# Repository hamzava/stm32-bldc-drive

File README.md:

# ⚡ Sensorless 3-Phase BLDC Motor Driver  
### Using STM32F411RE + IR2110 Gate Drivers + IRF3205

> 📌 **Recommended Reading:**  
> Please refer to `/Docs/BLDC Project Report.pdf` first for a detailed explanation of the architecture, technical challenges encountered, and lessons learned during development.  
> This repository documents a prototype exploration and does not represent a finalized, fully validated motor drive system.

◆ This project represents an exploration into low-level complementary PWM control, high-side bootstrap driving, and discrete 3-phase inverter design using STM32 advanced timers.

---

## ◆ Project Overview

🟥 This project is a  3-phase BLDC motor driver prototype built using:

 - **STM32F411RE** (Advanced Timer – Complementary PWM)
 - **IR2110 High/Low Side Gate Drivers**
 - IRF3205 N-Channel MOSFET Half-Bridges
 - Bootstrap High-Side Supply Topology

🟥 The objective was to implement manual commutation for a sensorless BLDC motor using complementary PWM outputs from the MCU’s advanced timer (TIM1), with register-level control and control the motor using it's BEMF.

This prototype focused on:

✔ BLDC Motor Control Algorithm
✔ Complementary PWM generation  
✔ Gate driver bootstrap behavior  
✔ Register-level commutation control  
✔ Hardware–firmware synchronization  

---
## ◆ Repository Structure
/Hardware
- ├── KiCad_Project
- ├── Gerbers
- ├── Schematics_PDF
- ├── PCB_Images

/Firmware

/Videos

/Docs
- ├── Datasheets
- ├── Resources_Used > ***All the files used to learn about technologies involved in this project***
- ├── BLDC Project Report.pdf

---

## ◆ Status

Prototype exploration complete.  
Further revision planned with improved instrumentation and driver selection.

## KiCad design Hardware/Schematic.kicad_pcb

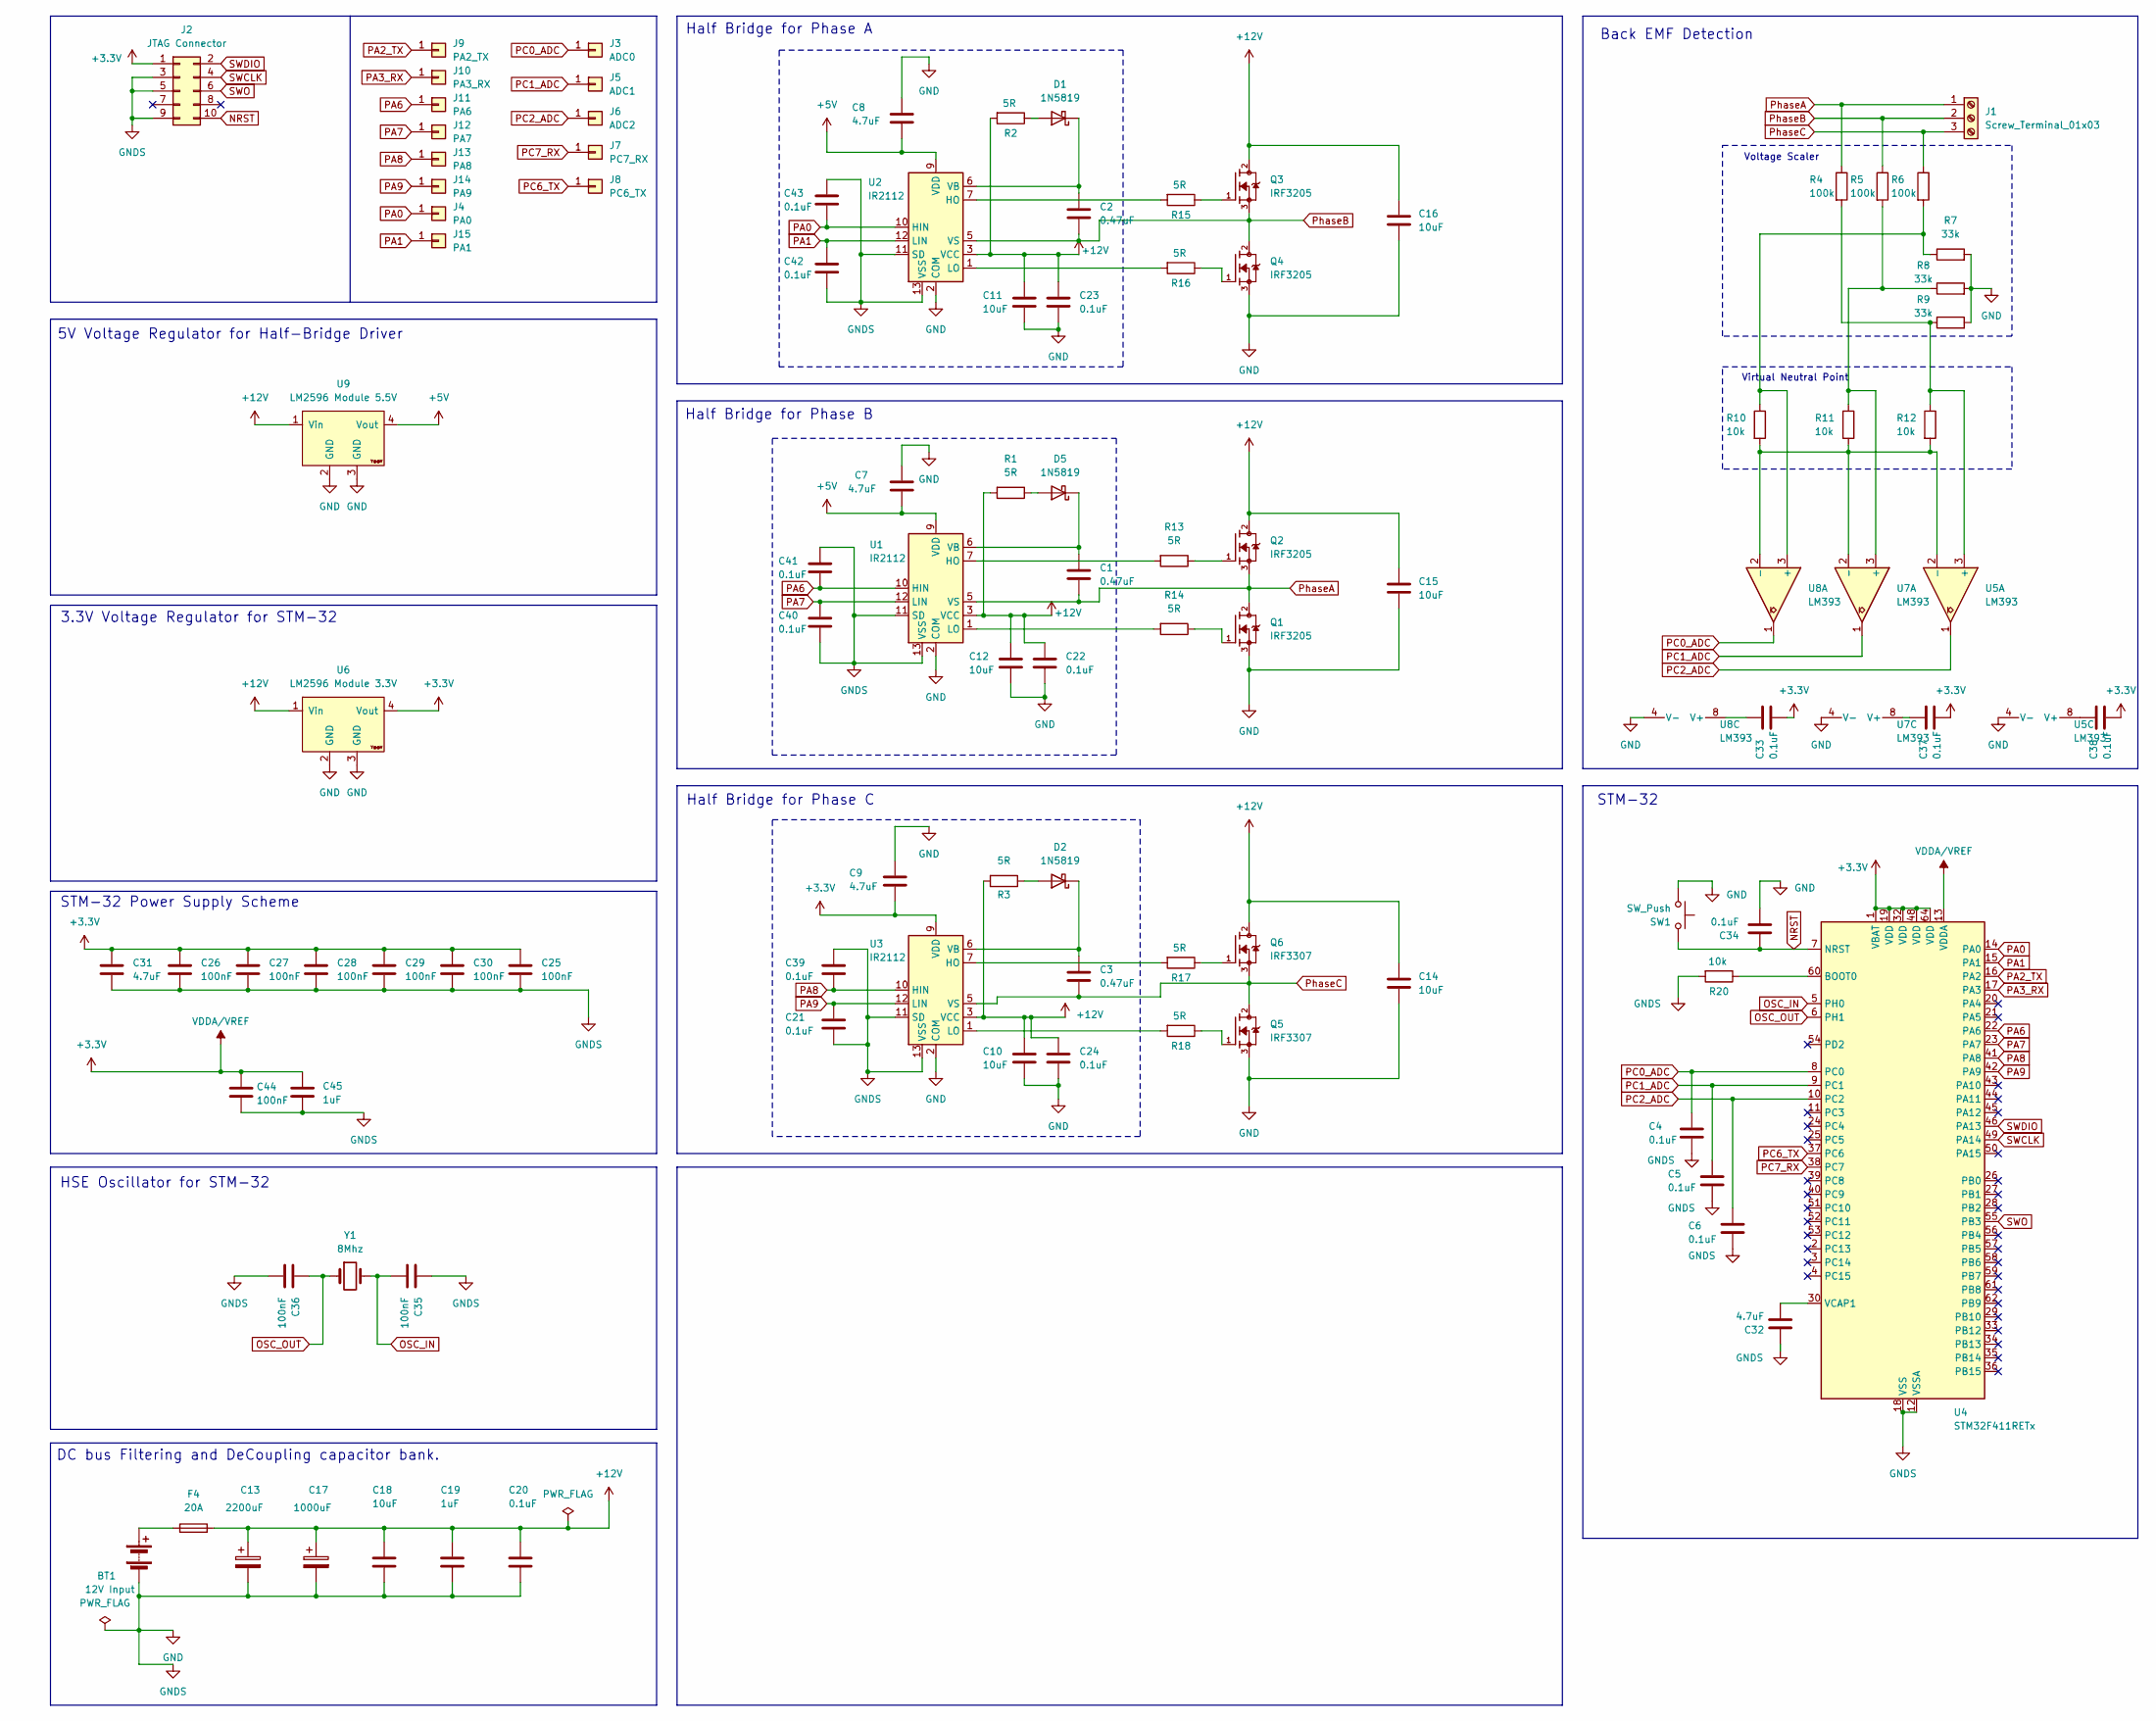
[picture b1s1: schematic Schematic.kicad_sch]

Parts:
BT1: 12V Input; AMASS_XT60-F_1x02_P7.20mm_Vertical
C1, C2, C3: 0.47uF; C_Disc_D4.3mm_W1.9mm_P5.00mm
C4, C5, C6, C20, C21, C22, C23, C24, C33, C34, C37, C38, C39, C40, C41, C42, C43: 0.1uF; C_Disc_D4.3mm_W1.9mm_P5.00mm
C7, C8, C9, C31, C32: 4.7uF; C_Disc_D4.3mm_W1.9mm_P5.00mm
C10, C11, C12, C14, C15, C16, C18: 10uF; C_Disc_D4.3mm_W1.9mm_P5.00mm
C13: 2200uF; CP_Radial_D10.0mm_P5.00mm
C17: 1000uF; CP_Radial_D8.0mm_P3.50mm
C19, C45: 1uF; C_Disc_D4.3mm_W1.9mm_P5.00mm
C25, C26, C27, C28, C29, C30, C35, C36, C44: 100nF; C_Disc_D4.3mm_W1.9mm_P5.00mm
D1, D2, D5: 1N5819; D_DO-35_SOD27_P7.62mm_Horizontal
F4: 20A; Fuseholder_Clip-5x20mm_Eaton_1A5601-01_Inline_P20.80x6.76mm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
J1: Screw_Terminal_01x03; TerminalBlock_MaiXu_MX126-5.0-03P_1x03_P5.00mm
J2: JTAG Connector; PinHeader_2x05_P2.54mm_Vertical
J3: ADC0; PinHeader_1x01_P1.00mm_Vertical
J4: PA0; PinHeader_1x01_P1.00mm_Vertical
J5: ADC1; PinHeader_1x01_P1.00mm_Vertical
J6: ADC2; PinHeader_1x01_P1.00mm_Vertical
J7: PC7_RX; PinHeader_1x01_P1.00mm_Vertical
J8: PC6_TX; PinHeader_1x01_P1.00mm_Vertical
J9: PA2_TX; PinHeader_1x01_P1.00mm_Vertical
J10: PA3_RX; PinHeader_1x01_P1.00mm_Vertical
J11: PA6; PinHeader_1x01_P1.00mm_Vertical
J12: PA7; PinHeader_1x01_P1.00mm_Vertical
J13: PA8; PinHeader_1x01_P1.00mm_Vertical
J14: PA9; PinHeader_1x01_P1.00mm_Vertical
J15: PA1; PinHeader_1x01_P1.00mm_Vertical
Q1, Q2, Q3, Q4: IRF3205; TO254P1041X444X2933-3; PARTREV 01/25/01
Q5, Q6: IRF3307; TO254P1041X444X2933-3; PARTREV 01/25/01
R1, R2, R3, R13, R14, R15, R16, R17, R18: 5R; R_Axial_DIN0207_L6.3mm_D2.5mm_P7.62mm_Horizontal
R4, R5, R6: 100k; R_Axial_DIN0207_L6.3mm_D2.5mm_P7.62mm_Horizontal
R7, R8, R9: 33k; R_Axial_DIN0207_L6.3mm_D2.5mm_P7.62mm_Horizontal
R10, R11, R12, R20: 10k; R_Axial_DIN0207_L6.3mm_D2.5mm_P7.62mm_Horizontal
SW1: SW_Push; SW_PUSH_6mm
U1, U2, U3: IR2112; DIP-14_W7.62mm
U4: STM32F411RETx; LQFP-64_10x10mm_P0.5mm
U5, U7, U8: LM393; DIP-8_W7.62mm_Socket
U6: LM2596 Module 3.3V; YAAJ_DCDC_StepDown_LM2596
U9: LM2596 Module 5.5V; YAAJ_DCDC_StepDown_LM2596
Y1: 8Mhz; Crystal_HC49-U_Vertical

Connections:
+3.3V: C9.2, C25.1, C26.1, C27.1, C28.1, C29.1, C30.1, C31.1, C33.2, C37.2, C38.2, C44.2, C45.2, J2.1, U3.9 (VDD), U4.1 (VBAT), U4.13 (VDDA), U4.19 (VDD), U4.32 (VDD), U4.48 (VDD), U4.64 (VDD), U6.4 (Vout)
+5V: C7.2, C8.2, U1.9 (VDD), U2.9 (VDD), U9.4 (Vout)
+12V: C10.1, C11.1, C12.1, C13.1, C14.1, C15.1, C16.1, C17.1, C18.1, C19.1, C20.1, C22.1, C23.1, C24.1, F4.2, Q2.2, Q3.2, Q6.2, R1.2, R2.2, R3.2, U1.3 (VCC), U2.3 (VCC), U3.3 (VCC), U6.1 (Vin), U9.1 (Vin)
GND: BT1.2 (-), C4.2, C5.2, C6.2, C7.1, C8.1, C9.1, C10.2, C11.2, C12.2, C13.2, C14.2, C15.2, C16.2, C17.2, C18.2, C19.2, C20.2, C21.2, C22.2, C23.2, C24.2, C25.2, C26.2, C27.2, C28.2, C29.2, C30.2, C31.2, C32.1, C34.2, C35.1, C36.2, C39.1, C40.2, C41.1, C42.2, C43.1, C44.1, C45.1, J2.3, J2.5, J2.9, Q1.3, Q4.3, Q5.3, R7.2, R8.2, R9.2, R20.2, SW1.1, U1.2 (COM), U1.11 (SD), U1.13 (VSS), U2.2 (COM), U2.11 (SD), U2.13 (VSS), U3.2 (COM), U3.11 (SD), U3.13 (VSS), U4.12 (VSSA), U4.18 (VSS), U4.31 (VSS), U4.47 (VSS), U4.63 (VSS), U5.4 (V-), U6.2 (GND), U6.3 (GND), U7.4 (V-), U8.4 (V-), U9.2 (GND), U9.3 (GND)
NRST: C34.1, J2.10, SW1.2, U4.7 (NRST)
unnamed: BT1.1 (+), F4.1
unnamed: D1.2 (A), R2.1
unnamed: C2.1, D1.1 (K), U2.6 (VB)
unnamed: D2.2 (A), R3.1
unnamed: C3.1, D2.1 (K), U3.6 (VB)
unnamed: D5.2 (A), R1.1
unnamed: C1.1, D5.1 (K), U1.6 (VB)
unnamed: Q1.1, R14.1
unnamed: Q2.1, R13.1
unnamed: Q3.1, R15.1
unnamed: Q4.1, R16.1
unnamed: Q5.1, R18.1
unnamed: Q6.1, R17.1
unnamed: R13.2, U1.7 (HO)
unnamed: R14.2, U1.1 (LO)
unnamed: R15.2, U2.7 (HO)
unnamed: R16.2, U2.1 (LO)
unnamed: R17.2, U3.7 (HO)
unnamed: R18.2, U3.1 (LO)
unnamed: R20.1, U4.60 (BOOT0)
unnamed: C32.2, U4.30 (VCAP1)
unnamed: R4.2, R9.1, R12.1, U5.3 (+)
unnamed: R10.2, R11.2, R12.2, U5.2 (-), U7.2 (-), U8.2 (-)
unnamed: C38.1, U5.8 (V+)
unnamed: R5.2, R8.1, R11.1, U7.3 (+)
unnamed: C37.1, U7.8 (V+)
unnamed: R6.2, R7.1, R10.1, U8.3 (+)
unnamed: C33.1, U8.8 (V+)
OSC_IN: C35.2, U4.5 (PH0), Y1.2
OSC_OUT: C36.1, U4.6 (PH1), Y1.1
PA0: C43.2, J4.1, U2.10 (HIN), U4.14 (PA0)
PA1: C42.1, J15.1, U2.12 (LIN), U4.15 (PA1)
PA2_TX: J9.1, U4.16 (PA2)
PA3_RX: J10.1, U4.17 (PA3)
PA6: C41.2, J11.1, U1.10 (HIN), U4.22 (PA6)
PA7: C40.1, J12.1, U1.12 (LIN), U4.23 (PA7)
PA8: C39.2, J13.1, U3.10 (HIN), U4.41 (PA8)
PA9: C21.1, J14.1, U3.12 (LIN), U4.42 (PA9)
PC0_ADC: C4.1, J3.1, U4.8 (PC0), U8.1
PC1_ADC: C5.1, J5.1, U4.9 (PC1), U7.1
PC2_ADC: C6.1, J6.1, U4.10 (PC2), U5.1
PC6_TX: J8.1, U4.37 (PC6)
PC7_RX: J7.1, U4.38 (PC7)
PhaseA: C1.2, J1.1, Q1.2, Q2.3, R4.1, U1.5 (VS)
PhaseB: C2.2, J1.2, Q3.3, Q4.2, R5.1, U2.5 (VS)
PhaseC: C3.2, J1.3, Q5.2, Q6.3, R6.1, U3.5 (VS)
SWCLK: J2.4, U4.49 (PA14)
SWDIO: J2.2, U4.46 (PA13)
SWO: J2.6, U4.55 (PB3)

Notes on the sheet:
HSE Oscillator for STM-32
STM-32 Power Supply Scheme
Virtual Neutral Point
STM-32
Back EMF Detection
Half Bridge for Phase A
DC bus Filtering and DeCoupling capacitor bank.
Voltage Scaler
5V Voltage Regulator for Half-Bridge Driver
Half Bridge for Phase B
Half Bridge for Phase C
3.3V Voltage Regulator for STM-32

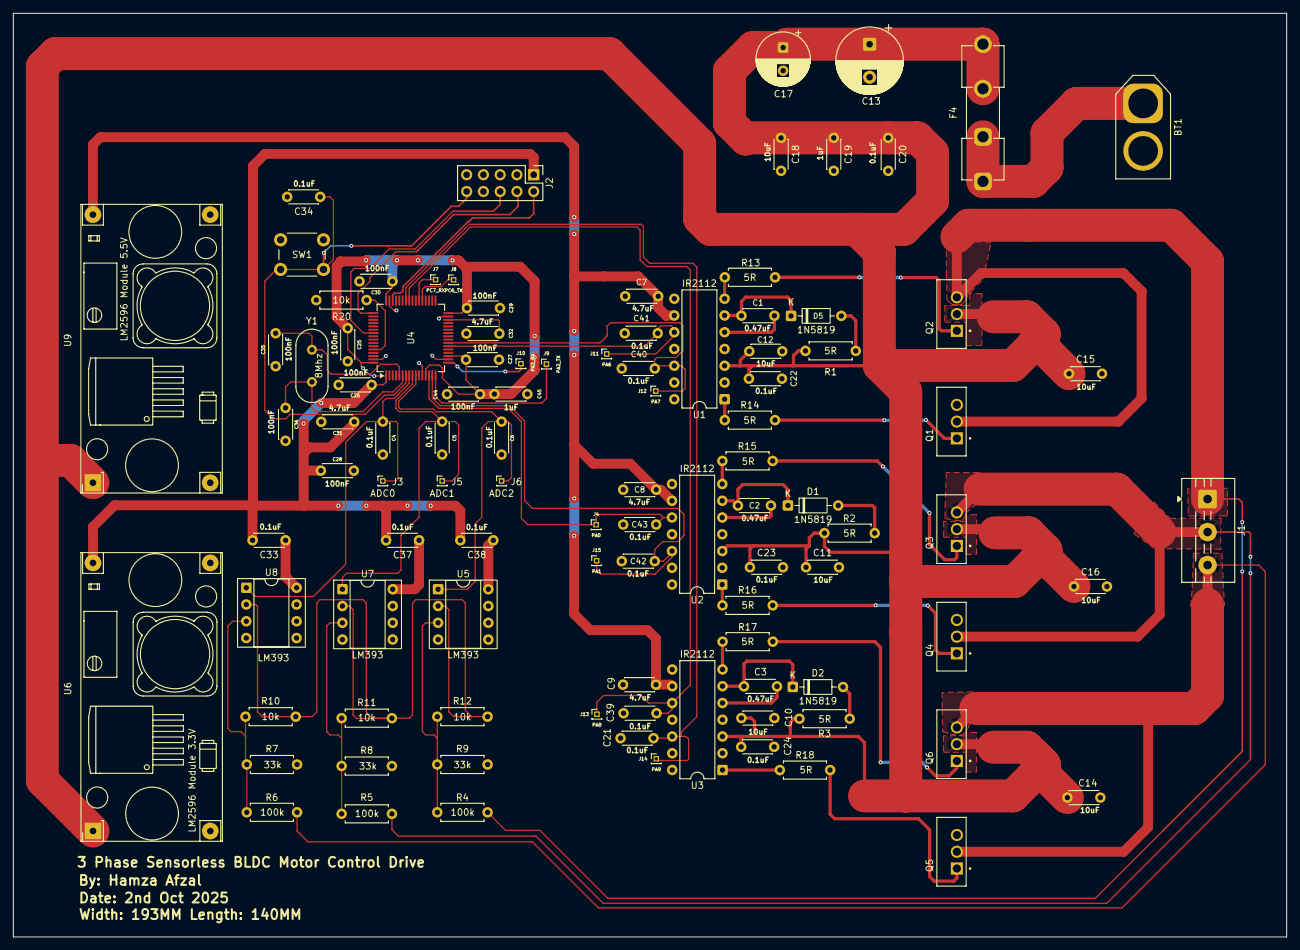
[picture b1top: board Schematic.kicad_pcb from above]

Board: 2 copper layers, 193.0 x 140.0 mm, 101 parts (0 on the bottom side), 54 nets.
